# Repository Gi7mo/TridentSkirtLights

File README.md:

# Voron Trident Skirt Lights #

**BOM**
|Part NO.  |Qty  |LCSC  |
|--|--|--|
| Conn_01x03 | 2 | C131339 |
| WS2812-2020 | 12 | C965555 |

**Assembly**
- Order the pcb at e.g. [pcbway](https://www.pcbway.com/project/shareproject/Trident_Skirt_Lights_6d030a0b.html) or [jlcpcb](https://jlcpcb.com/) (you need two for one printer)
    - Or just contact me via Discord "Gi7mo!#4618" i stil have some assembled boards left from my prototyping
- Order the parts at e.g. [lcsc](https://www.lcsc.com/)
- Print the new skirts (You WILL need supports)
- Print the new logo inserts (You WILL need supports)
- in the meantime, assemble the pcb
- Push in the new logo inserts in your skirts
- Push the pcb into the logo insert, no additional fasteing required
- Wire up the pcbs to your controller
- Add them as normal neopixels to your config
```
[neopixel my_skirts]
pin: YOUR_NEOPIXEL_PIN
chain_count: 24
initial_RED: 1.0
```

- 
- 

## Troubleshooting
- Problem: My Leds showing Random colors
    - Solution: Add a ~400Ω Resistor on the data line

## Notes
- You can contact me via Discord "Gi7mo!#4618"
- This readme file contains Amazon Associate, Aliexpress affiliate, PCBWay affiliate links. I make a comission on qualifying purchases.
- This project does not come with any warranty, if you choose to build/use one, you are doing this at your own risk!

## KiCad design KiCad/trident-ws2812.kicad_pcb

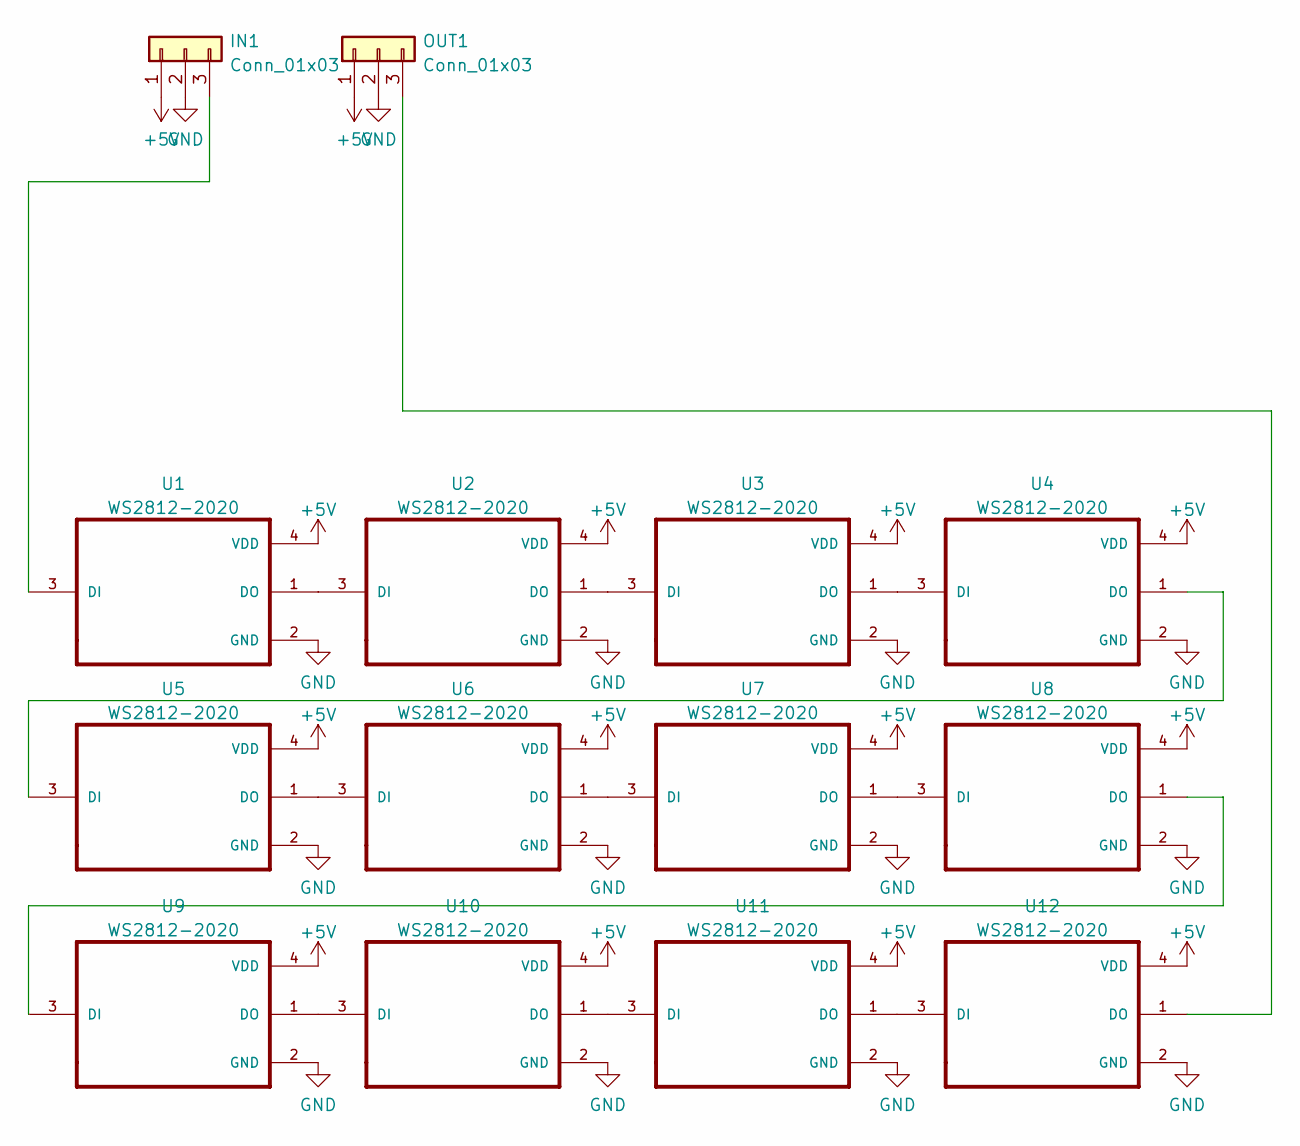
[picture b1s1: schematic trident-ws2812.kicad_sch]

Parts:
IN1: Conn_01x03; JST_PH_B3B-PH-K_1x03_P2.00mm_Vertical; LCSC C131339
OUT1: Conn_01x03; JST_PH_B3B-PH-K_1x03_P2.00mm_Vertical; LCSC C131339
U1, U2, U4, U5, U6, U7, U8, U9, U10, U11, U12: WS2812-2020; LED_WS2812-2020; LCSC C965555
U3: WS2812-2020; LED_WS2812-2020; LCSCL C965555

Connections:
+5V: IN1.1, OUT1.1, U1.4 (VDD), U2.4 (VDD), U3.4 (VDD), U4.4 (VDD), U5.4 (VDD), U6.4 (VDD), U7.4 (VDD), U8.4 (VDD), U9.4 (VDD), U10.4 (VDD), U11.4 (VDD), U12.4 (VDD)
GND: IN1.2, OUT1.2, U1.2 (GND), U2.2 (GND), U3.2 (GND), U4.2 (GND), U5.2 (GND), U6.2 (GND), U7.2 (GND), U8.2 (GND), U9.2 (GND), U10.2 (GND), U11.2 (GND), U12.2 (GND)
unnamed: IN1.3, U1.3 (DI)
unnamed: OUT1.3, U12.1 (DO)
unnamed: U1.1 (DO), U2.3 (DI)
unnamed: U2.1 (DO), U3.3 (DI)
unnamed: U3.1 (DO), U4.3 (DI)
unnamed: U4.1 (DO), U5.3 (DI)
unnamed: U5.1 (DO), U6.3 (DI)
unnamed: U6.1 (DO), U7.3 (DI)
unnamed: U7.1 (DO), U8.3 (DI)
unnamed: U8.1 (DO), U9.3 (DI)
unnamed: U10.1 (DO), U11.3 (DI)
unnamed: U9.1 (DO), U10.3 (DI)
unnamed: U11.1 (DO), U12.3 (DI)

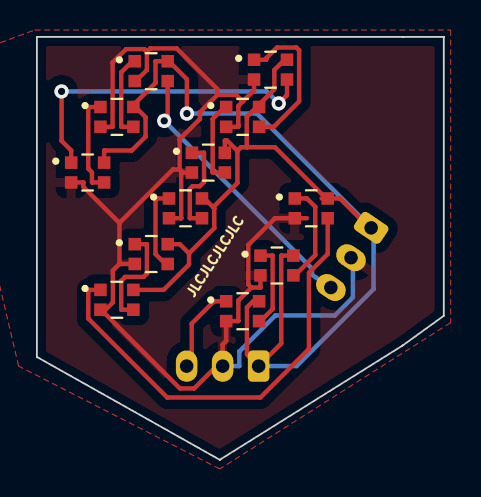
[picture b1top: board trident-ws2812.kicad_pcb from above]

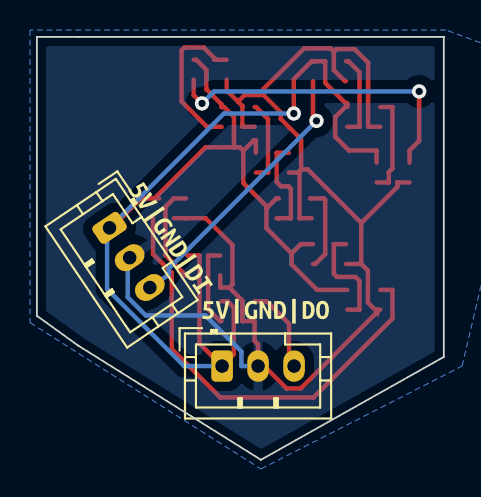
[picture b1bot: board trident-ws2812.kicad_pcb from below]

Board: 2 copper layers, 22.6 x 23.5 mm, 16 parts (4 on the bottom side), 15 nets.

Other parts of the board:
kibuzzard-62A46B00: G***; kibuzzard-62A46B00
kibuzzard-62A46BC2: G***; kibuzzard-62A46BC2

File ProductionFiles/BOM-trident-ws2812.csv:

Comment,Designator,Footprint,LCSC
Conn_01x03,"IN1,OUT1",JST_PH_B3B-PH-K_1x03_P2.00mm_Vertical,C131339
WS2812-2020,"U1,U10,U11,U12,U2,U3,U4,U5,U6,U7,U8,U9",LED_WS2812-2020,C965555

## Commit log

2022-07-07 add files
2022-07-10 add 300 and 350 skirts
2022-07-16 moarr infos
2022-08-23 add license file
2024-08-25 add skirt cad
